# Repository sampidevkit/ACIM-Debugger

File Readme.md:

# AC INDUCTION MOTOR - DEBUGGER BOARD

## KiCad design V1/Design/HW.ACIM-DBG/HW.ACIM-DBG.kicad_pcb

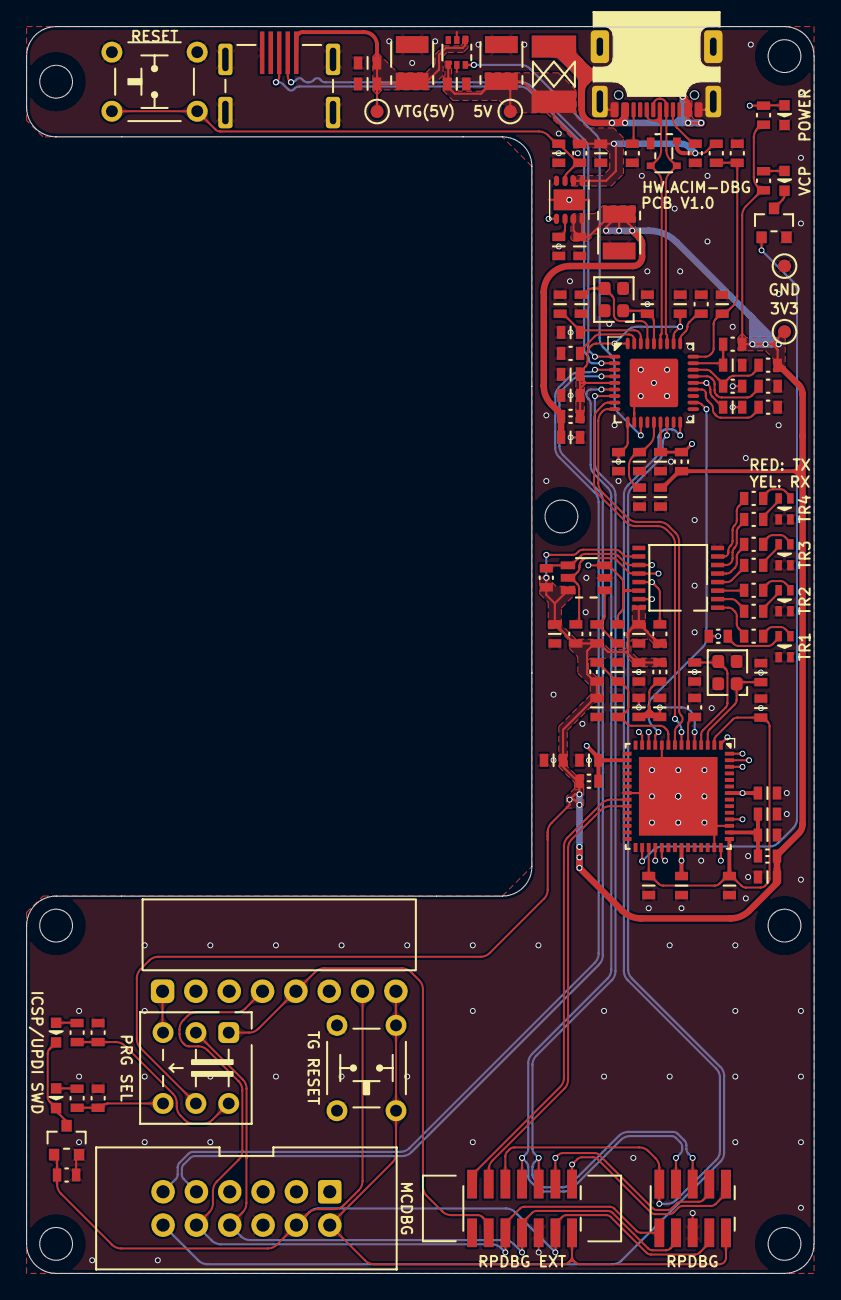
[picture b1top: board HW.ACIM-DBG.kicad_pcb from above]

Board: 4 copper layers, 60.0 x 95.0 mm, 125 parts (0 on the bottom side), 88 nets.

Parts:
BT1: RESET; BUTTON_4P_6x6
BT3: TG RESET; BUTTON_4P_6x6
C1, C2, C4, C5, C10, C15, C17, C31, C38, C40, C41, C42, C43, C44, C48, C49, C50, C52, C53: 100nF; CAP0603
C3: 220uF; CAP1411
C6, C26: 4.7uF; CAP1411
C7, C8, C9, C13, C19, C20, C21, C22, C39: 22pF; CAP0603
C11, C12, C14, C16, C34, C35, C37: 10nF; CAP0603
C27, C36, C45, C46, C47, C54: 10uF; CAP0603
C55, C56: 10pF; CAP0603
D1: TVS 5.5V; SOT143B_NEXT
D2: VCP; LED0603
D3: POWER; LED0603
D5: ICSP/UPDI; LED0603
D6: SWD; LED0603
D7: TR4; LED0606_4P
D8: TR3; LED0606_4P
D9: TR2; LED0606_4P
D10: TR1; LED0606_4P
F1: 750mA; FUSE1812
FT1, FT2, FT3, FT4, FT5, FT6: 120R@100MHz; FT0603
H1: RPDBG EXT; DIL14-1.27-SMD
H2: RPDBG; DIL10-1.27-SMD
J1: USB C; USB4105
J3: SNAP PINOUT; HDF1x8x2.54_TH_RA
J4: MICRO USB; ZX60-B-5S(31)
J5: MCDBG; IDC-2x6x2.54MM_TH
Q1, Q2: MFET N; SOT23
R1, R2: 5.1K; RES0603
R3, R10, R19, R20, R25: 100K; RES0603
R5, R18, R28, R34, R35, R38, R39, R47: 10K; RES0603
R6, R46: 12K; RES0603
R7, R8, R9: 47K; RES0603
R11, R21, R22, R27, R49, R50, R51, R52, R53, R54, R55, R56: 1K; RES0603
R29: 2.2K; RES0603
SH1, SH2, SH3, SH4, SH5, SH6, SH7: SCREW HOLDER; SCREWHOLE-2.5M
SW1: PRG SEL; SW_PUSH_2DPDT
TP3: 5V; TP1MM
TP4: VTG(5V); TP1MM
TP5: 3V3; TP1MM
TP6: GND; TP1MM
U1: LDO 3.3V; DFN8_3x3_MCHP
U2: USB HUB 2.0 4-CH; SQFN36_6x6_MCHP
U3: SPI EEPROM; SOT-23-6_MCHP
U7: LOAD SWITCHER; SOT363
U8: FT4232H; VQFN-56_FTDI
U9: SHIFT REG 8BIT; TSSOP16-SOT403-1
U10: 12MHz; CDFN2520-ABM10
Y1: 24MHz; CDFN2520-ABM10

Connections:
+3V3: C2.2, C6.+, C8.2, C13.2, C19.2, C20.2, C21.2, C22.2, C49.2, C50.2, FT1.1, FT2.1, FT3.1, FT4.1, FT5.1, FT6.1, R5.1, R8.2, R11.2, R27.1, R28.2, R38.2, R39.2, R47.2, SW1.5 (COM2), TP5.1, U1.7 (SEN/ADJ), U1.8 (VOUT), U3.6 (VCC), U9.10 (~MR), U9.16 (VCC)
+5V: C3.+, C4.2, C31.2, D1.4 (VCC), F1.2, R18.2, R34.1, TP3.1, U1.1 (VIN1), U1.2 (VIN2), U7.4 (VIN)
/TERMINALS/AUX_RXD1: H1.13 (ARX), U8.22 (BDBUS0/TXD)
/TERMINALS/AUX_RXD2: J5.7 (DV_RXD), U8.12 (ADBUS0/TXD)
/TERMINALS/AUX_TXD1: H1.11 (ATX), U8.23 (BDBUS1/RXD)
/TERMINALS/AUX_TXD2: J5.5 (DV_TXD), U8.13 (ADBUS1/RXD)
/TERMINALS/DBG_RXD1: H1.3 (DBG_RX), H2.3 (DBG_RX), U8.42 (DDBUS0/TXD)
/TERMINALS/DBG_RXD2: J5.3 (DB_RXD), U8.32 (CDBUS0/TXD)
/TERMINALS/DBG_TXD1: H1.1 (DBG_TXD), H2.1 (DBG_TXD), U8.46 (DDBUS1/RXD)
/TERMINALS/DBG_TXD2: J5.1 (DB_TXD), U8.33 (CDBUS1/RXD)
/TERMINALS/PGC: H1.10 (PGC/SWCLK), H2.10 (PGC/SWCLK), J3.4, J5.10 (PGC/SWDCK)
/TERMINALS/PGD: H1.8 (PGD/SWDIO/UPDI), H2.8 (PGD/SWDIO/UPDI), J5.8 (PGD/SWDIO), SW1.2 (COM1)
/TERMINALS/PRG_USB_N: J4.2 (D-), U2.1 (USBDM_DN1)
/TERMINALS/PRG_USB_P: J4.3 (D+), U2.2 (USBDP_DN1)
/TERMINALS/PRG_VBUS: U2.12 (PRTPWR1/BC_EN1), U7.6 (EN)
/TERMINALS/SWO: H1.12 (PGM/SWO), J3.5, SW1.1 (NC1)
/TERMINALS/USB_MC_N: J5.11 (USB_DM), U2.3 (USBDM_DN2)
/TERMINALS/USB_MC_P: J5.9 (UDB_DP), U2.4 (USBDP_DN2)
/TERMINALS/USB_MC_VBUS: J5.12 (VBUS), U2.16 (PRTPWR2/BC_EN2)
/TERMINALS/USB_RP_N: H1.7 (USB_DM), H2.7 (USB_DM/ARX), U2.6 (USBDM_DN3)
/TERMINALS/USB_RP_P: H1.5 (USB_DP), H2.5 (USB_DP/ATX), U2.7 (USBDP_DN3)
/TERMINALS/USB_RP_VBUS: H1.9 (USB_VBUS), H2.9 (USB_VBUS), U2.18 (PRTPWR3/BC_EN3)
/TERMINALS/VDD_SEN: H1.4 (VDD), H2.4 (VDD), J3.7, J5.4 (VDD), Q2.1 (G), R3.2
/TERMINALS/~MCLR: BT3.1, BT3.2, H1.2 (~MCLR/~RESET), H2.2 (~MCLR/~RESET), J3.8, J5.2 (~RESET)
/USB HUB/USB4_N: U2.8 (USBDM_DN4), U8.7 (DM)
/USB HUB/USB4_P: U2.9 (USBDP_DN4), U8.8 (DP)
/USB HUB/USB4_VBUS: U2.20 (PRTPWR4/BC_EN4), U8.11 (~RESET)
/USB HUB/USB_N: D1.3 (I/O2), J1.A7 (DN1), J1.B7 (DN2), U2.30 (USBDM_UP)
/USB HUB/USB_P: D1.2 (I/O1), J1.A6 (DP1), J1.B6 (DP2), U2.31 (USBDP_UP)
/USB HUB/XTALIN: C9.2, U2.33 (XTALIN/CLKIN), Y1.3
/USB HUB/XTALOUT: C7.2, U2.32 (XTALOUT), Y1.1
/VCP/EECLK: R28.1, U3.4 (CLK), U8.56 (EECLK), U9.11 (SHCP)
/VCP/EECS: R39.1, U3.5 (CS), U8.1 (EECS), U9.12 (STCP)
/VCP/EEDATA: R29.1, U3.3 (DI), U8.55 (EEDATA), U9.14 (DS)
/VCP/OSCI: C55.2, U8.3 (OSCI), U10.1 (X1)
/VCP/OSCO: C56.2, U8.4 (OSCO), U10.3 (GND2)
/VCP/~PWREN: R47.1, U8.54 (~PWREN), U9.13 (~OE)
GND: BT1.3, BT1.4, BT3.3, BT3.4, C1.1, C2.1, C3.-, C4.1, C5.2, C6.-, C7.1, C8.1, C9.1, C10.1, C11.1, C12.1, C13.1, C14.1, C15.1, C16.1, C17.1, C19.1, C20.1, C21.1, C22.1, C26.-, C27.1, C31.1, C34.1, C35.1, C36.1, C37.1, C38.1, C39.1, C40.1, C41.1, C42.1, C43.1, C44.1, C45.1, C46.1, C47.1, C48.1, C49.1, C50.1, C52.1, C53.1, C54.1, C55.1, C56.1, D1.1 (GND), D3.K, D7.1 (GK), D7.4 (RK), D8.1 (GK), D8.4 (RK), D9.1 (GK), D9.4 (RK), D10.1 (GK), D10.4 (RK), H1.6 (GND), H2.6 (GND), J1.A1B12 (GND), J1.B1A12 (GND), J1.S1, J1.S2, J1.S3, J1.S4, J3.6, J4.5 (GND), J4.6 (CASE), J4.7 (CASE), J4.8 (CASE), J4.9 (CASE), J5.6 (GND), Q1.2 (S), Q2.2 (S), R1.1, R2.1, R3.1, R6.2, R7.2, R9.1, R10.1, R19.1, R20.1, R25.1, R35.2, R46.2, TP6.1, U1.4 (GND), U1.9 (EP), U2.11 (TEST), U2.37 (VSS), U3.2 (VSS), U7.2 (GND), U7.5 (GND), U8.10 (TEST), U8.21 (GND), U8.41 (GND), U8.45 (GND), U8.57 (TP), U9.8 (GND), U10.2 (GND1), U10.4 (X2), Y1.2, Y1.4
unnamed: C11.2, C14.2, C34.2, C37.2, FT1.2, U2.5 (VDDA33), U2.10 (VDDA33), U2.29 (VDDA33), U2.36 (VDDA33)
unnamed: C16.2, C36.2, FT2.2, U2.15 (VDD33), U2.23 (VDD33)
unnamed: C40.2, C44.2, C48.2, FT3.2, U8.16 (VCCIO), U8.36 (VCCIO), U8.50 (VCCIO)
unnamed: D2.A, R27.2
unnamed: D5.A, R21.1
unnamed: D6.A, R22.1
unnamed: D7.2 (GA), R50.2
unnamed: D7.3 (RA), R49.2
unnamed: D8.2 (GA), R52.2
unnamed: D8.3 (RA), R51.2
unnamed: D9.2 (GA), R54.2
unnamed: D9.3 (RA), R53.2
unnamed: D10.2 (GA), R56.2
unnamed: D10.3 (RA), R55.2
unnamed: F1.1, J1.A4B9 (VBUS), J1.B4A9 (VBUS)
unnamed: J1.A5 (CC1), R2.2
unnamed: J1.B5 (CC2), R1.2
unnamed: D2.K, Q1.3 (D)
unnamed: Q1.1 (G), U8.30 (~SUSPEND)
unnamed: D5.K, D6.K, Q2.3 (D)
unnamed: R19.2, R21.2, SW1.4 (NC2)
unnamed: J3.1, SW1.3 (NO1)
unnamed: R20.2, R22.2, SW1.6 (NO2)
unnamed: C5.1, U1.6 (CDELAY)
unnamed: D3.A, R11.1, U1.5 (PWRGD)
unnamed: BT1.1, BT1.2, C17.2, R18.1, U1.3 (~SHDN)
unnamed: C10.2, C12.2, U2.14 (CRFILT)
unnamed: R8.1, R25.2, U2.25 (HS_IND/CFG_SEL1)
unnamed: C15.2, C35.2, U2.34 (PLLFILT)
unnamed: R6.1, U2.35 (RBIAS)
unnamed: R10.2, U2.24 (SCL/SMBCLK/CFG_SEL0)
unnamed: R7.1, U2.22 (SDA/SMBDATA/NON_REM1)
unnamed: R9.2, U2.28 (SUSP_IND/LOCAL_PWR/NON_REM0)
unnamed: C39.2, R34.2, R35.1, U2.27 (VBUS_DET)
unnamed: C38.2, R5.2, U2.26 (~RESET)
unnamed: R29.2, R38.1, U3.1 (DO)
unnamed: R46.1, U8.6 (REF)
unnamed: C43.2, C47.2, FT6.2, U8.5 (VPHY)
unnamed: C42.2, C46.2, FT5.2, U8.9 (VPLL)
unnamed: C41.2, C45.2, FT4.2, U8.44 (VREGIN)
unnamed: C52.2, C53.2, C54.2, U8.2 (VCORE), U8.31 (VCORE), U8.43 (VREGOUT)
unnamed: R55.1, U9.15 (Q0)
unnamed: R56.1, U9.1 (Q1)
unnamed: R53.1, U9.2 (Q2)
unnamed: R54.1, U9.3 (Q3)
unnamed: R51.1, U9.4 (Q4)
unnamed: R52.1, U9.5 (Q5)
unnamed: R49.1, U9.6 (Q6)
unnamed: R50.1, U9.7 (Q7)
VTG: C1.2, C26.+, C27.2, J4.1 (VCC), TP4.1, U7.1 (VOUT)

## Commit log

2024-09-25 Initialize
2024-09-25 V0 production files
2024-09-25 V1 schematic
2024-09-26 V0.1 production files
2024-12-03 V1 schematic update 1
2024-12-04 V1 schematic update 2
2024-12-05 V1 schematic update 3
2024-12-08 V1 layout
2024-12-10 V1 layout update 1
2024-12-16 V1 layout update 2
2024-12-16 V1 layout update 3
2024-12-16 V1 layout update 4
2024-12-19 V1 layout update 5
2025-01-04 V1 layout update 6
2025-01-06 V1 layout update 7
2025-01-08 V1 layout update 8
2025-01-20 V1 layout update 9
2025-01-21 V1 layout update 10
2025-01-22 V1 layout update 11
2025-01-25 V1 layout update 12
2025-01-26 V1 layout update 13
2025-01-27 V1 layout update 14
2025-02-03 V1 layout update 15
2025-02-04 V1 layout update 16
2025-02-06 Production HW.ACIM-DBG_V1.0
2025-03-21 Production HW.ACIM-DBG_V1.0 update BoM
2025-03-22 Production HW.ACIM-DBG_V1.0 update 3D, USB drivers
